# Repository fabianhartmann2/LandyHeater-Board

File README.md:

# LandyHeater Board

Hardwareentwicklung für das Landy-Heater-Steuergerät auf Basis des `ESP32-S3-WROOM-1U-N16R8`.

## Aktueller Stand

Revision A hat Phase 0 und Phase 1 abgeschlossen. Der Phase-2-Schaltplan wurde nach dem zurückgewiesenen rasterartigen Erstentwurf grundlegend als zusammenhängender Engineering-Schaltplan neu aufgebaut. Alle sieben A4-Seiten wurden aus dem KiCad-Export einzeln visuell geprüft; lokale Funktionsnetze werden mit sichtbaren Leitungen dargestellt. ERC, Struktur-Audit und der elektrische Vorher-/Nachher-Netzlistenvergleich sind fehlerfrei. Die normative Grundlage ist Dokumentversion 1.6. Phase 2 bleibt wegen der im Review dokumentierten Mess-, Transienten-, FPC- und Footprint-Gates sowie der noch ausstehenden ausdrücklichen Abnahme **nicht freigegeben**; Phase 3 wurde nicht begonnen.

- [Hardware-Anforderungsspezifikation Revision A](docs/Hardware-Anforderungsspezifikation_Revision_A.md)
- [Ergebnisbericht Phase 0](docs/Phase_0_KiCad-Arbeitsumgebung.md)
- [Phase 1 – Architektur und Bauteilfestlegung](docs/Phase_1_Architektur-und-Bauteilfestlegung.md)
- [Phase 2 – KiCad-Schaltplan und Review](docs/Phase_2_Schaltplanreview.md)
- [Phase 2 – Anforderungs- und Schnittstellenliste](docs/Phase_2_Anforderungs-und-Schnittstellenliste.md)
- [Phase 2 – Quellen und Rückverfolgbarkeit](docs/Phase_2_Quellen-und-Rueckverfolgbarkeit.md)
- [GPIO-Matrix Revision A](docs/GPIO-Matrix_Revision_A.md)
- [Leistungs- und Ruhestrombudget Revision A](calculations/Leistungs-und-Ruhestrombudget_Revision_A.md)
- [Phase 2 – Worst-Case-Berechnungen](calculations/Phase_2_Worst-Case-Berechnungen.md)
- [Schaltplan-PDF Phase 2](output/pdf/LandyHeater-Board-schematic-Phase2.pdf)
- [Vorläufige BOM Phase 2](output/bom/LandyHeater-Board-BOM-Phase2.csv)
- [ERC-Bericht Phase 2](output/reports/LandyHeater-Board-ERC-Phase2.rpt)
- [Netzlisten-/BOM-Audit Phase 2](output/reports/LandyHeater-Board-Audit-Phase2.txt)
- [Netzlistenvergleich vor/nach grafischer Überarbeitung](output/reports/LandyHeater-Board-Netlist-Comparison-Phase2.txt)

Die Spezifikation definiert Funktionsumfang, Schnittstellen, Versorgung, Mechanik, sichere Hardwarezustände, Layoutregeln, Fertigungsunterlagen und Abnahmetests. Die darin aufgeführten Verifikationspunkte müssen vor der Fertigungsfreigabe abgeschlossen werden.

## Phasenplan Revision A

Jede Phase wird einzeln beauftragt, geprüft und freigegeben. Mit der nächsten Phase wird erst nach ausdrücklicher Freigabe der Ergebnisse begonnen. Erkenntnisse, die Anforderungen verändern, werden zuerst in der Hardware-Anforderungsspezifikation dokumentiert.

### Phase 0 – KiCad-Arbeitsumgebung und Projektgerüst

- KiCad-10-Version und Kommandozeilenwerkzeuge prüfen und dokumentieren.
- Verzeichnisstruktur für KiCad-Quellen, lokale Symbole, Footprints, 3D-Modelle, Berechnungen und Fertigungsdaten anlegen.
- Leeres KiCad-Projekt mit vier Lagen, Revision, Titelblock und grundlegenden Netzklassen erstellen.
- Reproduzierbare Prüf- und Exportbefehle vorbereiten.

**Freigabepunkt:** Das Projekt lässt sich ohne fehlende Bibliotheken öffnen und die automatischen KiCad-Prüfwerkzeuge sind verfügbar.

**Status:** Technisch abgeschlossen und durch den Auftraggeber am 06.09.2026 mit dem Auftrag zum Beginn von Phase 1 freigegeben.

### Phase 1 – Schaltungsarchitektur und Bauteilfestlegung

- Blockschaltbild, Versorgungskonzept und Spannungsdomänen finalisieren.
- Vollständige ESP32-GPIO-Matrix einschließlich Reset-, Boot- und Deep-Sleep-Zuständen erstellen.
- Strom-, Ruhestrom-, Verlustleistungs- und USB-Lastbudget erstellen.
- Konkrete Herstellerteilenummern für aktive Bauteile, Schutzbeschaltung, Steckverbinder und FPC-Stecker auswählen.
- Footprints, Pinouts, Temperaturbereiche und PCBWay-Beschaffbarkeit vorprüfen.

**Freigabepunkt:** Architektur, GPIO-Matrix, Bauteilauswahl und Berechnungen sind nachvollziehbar dokumentiert; offene Punkte für den Schaltplan sind geschlossen oder ausdrücklich als Verifikationspunkte gekennzeichnet.

**Status:** Technisch abgeschlossen und durch den Auftraggeber am 06.09.2026 mit dem Auftrag zum Beginn von Phase 2 freigegeben.

### Phase 2 – KiCad-Schaltplan

- Hierarchischen Schaltplan für Versorgung, ESP32/USB, Display/Touch/Frontlicht, RTC, AUTOTERM, 1-Wire, Taster/LED und Diagnoseanzeige erstellen.
- Lokale Symbole und Footprint-Zuordnungen vollständig einbinden.
- Sichere Hardwarezustände, Testpunkte und Bestückungsoptionen abbilden.
- ERC durchführen und alle Warnungen entweder beheben oder schriftlich begründen.
- Schaltplan-PDF und vorläufige BOM für den Review erzeugen.

**Freigabepunkt:** Schaltplanreview abgeschlossen, ERC ohne ungeklärte Fehler und alle Hersteller-Pinouts unabhängig geprüft.

**Status:** Grafischer Neuaufbau, interner A4-Sichtreview und elektrischer Review abgeschlossen. ERC, exportierter Netzlisten-/BOM-Audit und Vorher-/Nachher-Topologievergleich sind fehlerfrei. Phase 2 ist dennoch nicht freigegeben, bis die in `docs/Phase_2_Schaltplanreview.md` aufgeführten Freigabesperren geschlossen und der Schaltplan ausdrücklich abgenommen ist.

### Phase 3 – Mechanik und Platzierung

- PCB-Kontur, Befestigungspunkte und zulässigen Bauraum festlegen.
- Display, drei FPC-Stecker, Nano-Fit-Anschlüsse, USB-C, Antennenkoax, Knopfzelle sowie BOOT-, RESET- und DIAG-Taster platzieren.
- Energiefluss-Diagnoseanzeige und gegebenenfalls zwei optionale Status-LEDs integrieren.
- Kritische Keep-outs, FPC-Biegeradien, Steck-/Entriegelungswege und Servicezugang prüfen.
- Vollständig bestücktes 3D-STEP-Modell für Gehäuse- und Kollisionsprüfung erzeugen.

**Freigabepunkt:** Platzierungs- und 3D-Review abgeschlossen; Gehäuseschnittstellen, Bedienung und Wartungszugang sind freigegeben.

### Phase 4 – Vierlagen-PCB-Layout

- Finalen PCBWay-Stackup und Netzklassen übernehmen.
- Versorgungsschutz, Buck-Regler, USB, ESP32, E-Paper-Booster und weitere Signale nach Priorität routen.
- Durchgehende GND-Referenz, Rückstrompfade, Abblockung, EMI-Abstände und thermische Reserven sicherstellen.
- DRC, ERC-Rückprüfung, Layoutchecklisten und visuellen Lagenreview durchführen.

**Freigabepunkt:** DRC ohne ungeklärte Fehler; Schaltplan, PCB, Pin-Matrix und BOM sind synchron und der Layoutreview ist dokumentiert.

### Phase 5 – PCBWay-Fertigungsfreigabe

- RS-274-X-Gerber, Excellon-Bohrdaten und gegebenenfalls ODB++/IPC-D-356 erzeugen.
- PCBWay-BOM und CPL/Centroid-Dateien mit Seite, Position und Rotation erstellen.
- Schaltplan, Bestückungszeichnungen, Fertigungszeichnung, DNP-Liste, STEP-Modell und spezielle Prozesshinweise beilegen.
- Gerber, Bohrungen, Lötstoppmaske, Pastenlagen, Silkscreen, Bauteilrotationen und Pin 1 unabhängig kontrollieren.
- Getrennte, eindeutig versionierte ZIP-Pakete für PCB-Fertigung und PCBA zusammenstellen.

**Freigabepunkt:** Manufacturing-Release-Checkliste vollständig; erst danach dürfen die fünf Prototypen bei PCBWay bestellt werden.

### Phase 6 – Inbetriebnahme der fünf Prototypen

- Sicht-, Kurzschluss- und Widerstandsprüfung vor dem ersten Einschalten.
- Versorgungsschienen mit strombegrenzten Laborquellen stufenweise prüfen.
- ESP32-Reset, Boot und USB-Programmierung verifizieren.
- Diagnoseanzeige, Deep-Sleep, RTC, Touch, Display, Frontlicht, 1-Wire und AUTOTERM in definierter Reihenfolge testen.
- Ruhestrom, Lastsprünge, Rückspeisung, Temperaturverhalten und alle Abnahmekriterien protokollieren.
- Abweichungen sammeln und Entscheidung über Nacharbeit oder Revision B treffen.

**Freigabepunkt:** Vollständiger Prüfbericht für alle fünf Prototypen und dokumentierte Entscheidung über den weiteren Einsatz.

### Geplante Endergebnisse

- editierbares KiCad-Projekt mit projektlokalen Bibliotheken,
- Schaltplan und Bestückungszeichnungen als PDF,
- vollständige BOM und GPIO-Matrix,
- PCB-Layout und 3D-STEP-Modell,
- Gerber-, Drill-, CPL-/Centroid- und PCBWay-BOM-Dateien,
- Fertigungs- und PCBA-ZIP-Pakete,
- Prüfplan und Prototypen-Prüfbericht.

## Abgrenzung Revision A

Revision A umfasst die AUTOTERM-UART-Schnittstelle, drei gemeinsam angeschlossene DS18B20-Sensoren, RTC, USB-C, externen Taster mit dimmbarer LED, eine lokale Energiefluss-Diagnoseanzeige sowie das Good-Display-E-Paper mit Touch und Frontlicht. VOTRONIC VBCS und Smart-Shunt sind für eine spätere Revision vorgemerkt.

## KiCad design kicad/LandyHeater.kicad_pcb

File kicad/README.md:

# LandyHeater Controller – KiCad-Projekt (Rev B)

Neuaufbau nach [Anforderungsdokument v2.0](../docs/Anforderungsdokument_Neuentwicklung.md). Aus dem bisherigen Repository wurden keine KiCad-Dateien, Bibliotheken oder Skripte übernommen (N-01).

## Stand

| Phase | Status |
|---|---|
| 0 – Projekt, Lagen, Regeln, Bibliotheken | freigegeben (2026-10-12) |
| 1 – Bauteilauswahl, Symbole, Footprints | freigegeben (2026-10-12) – [Bauteilliste](Bauteilliste.md) |
| 2 – Schaltplan | freigegeben (2026-10-13) – [Review](Phase2_Schaltplanreview.md), [Entwurf](Schaltungsentwurf.md) |
| 3 – Platzierung (Meilenstein nach [Layout-Anleitung](../docs/PCB_Layout_Engineering_Instructions.md)) | Schritt 1–2 freigegeben: [Analyse und Floorplan](Platzierung_1_Analyse_Floorplan.md) · Schritt 3–5 freigegeben (2026-10-14): [Platzierungsbericht](Platzierung_2_Bericht.md) · Schritt 6 Routing in Arbeit · [Transientennachweis V-01](Phase3_Platzierung.md#6-transientennachweis-v-01-p-03) |

## Struktur

| Pfad | Inhalt |
|---|---|
| `LandyHeater.kicad_pro/.kicad_sch/.kicad_pcb` | Projekt, Schaltplan, Leiterplatte (KiCad 10.0) |
| `libraries/LandyHeater.kicad_sym` | projektlokale, geprüfte Symbole (Bibliothek `LandyHeater`) |
| `libraries/LandyHeater.pretty/` | projektlokale, geprüfte Footprints (Bibliothek `LandyHeater`) |
| `libraries/3dmodels/` | 3D-Modelle, im Projekt als `${LANDYHEATER_3DMODELS}` |
| `tools/` | reproduzierbare KiCad-Python-Werkzeuge: Floorplan, Platzierung, Platzierungsprüfung, Ratsnest-Kennzahlen, Footprint-Aktualisierung |
| `sim/` | SPICE-Nachweise (ngspice aus KiCad) |
| `doc/` | Renderings für die Berichte |
| `output/` | erzeugte Berichte und Fertigungsdaten (nicht versioniert) |

## Leiterplatte

- 4 Lagen, JLCPCB-Stackup **JLC04161H-7628**, 1,6 mm, ENIG:
  F.Cu 35 µm · Prepreg 7628 0,2104 mm (εr 4,4) · In1.Cu 15,2 µm · Kern 1,065 mm · In2.Cu 15,2 µm · Prepreg 0,2104 mm · B.Cu 35 µm.
- Lagennutzung (A14): F.Cu Bauteile/Signale, In1.Cu GND durchgehend, In2.Cu Versorgung/langsame Signale, B.Cu GND/langsame Signale.
- Kontur: 80 × 50 mm, Ecken R 2 mm, Ursprung (100, 100). Vier M3-Befestigungslöcher H1–H4 (3,2 mm, nur Leiterplatte) in den Ecken, drei Passermarken FID1–FID3.

## Designregeln (JLCPCB 4 Lagen, mit Reserve)

| Regel | Wert | JLCPCB-Minimum |
|---|---|---|
| Leiterbahn Standard / Minimum | 0,2 / 0,127 mm | 0,09 mm |
| Abstand Kupfer | 0,2 mm (Regel), in Feinraster-ICs 0,12 mm | 0,09 mm |
| Via Standard | 0,6 / 0,3 mm | 0,45 / 0,3 mm (ohne Aufpreis) |
| Via Minimum | 0,45 / 0,3 mm | – |
| Kupfer zum Platinenrand | 0,3 mm | 0,2 mm |
| Bohrung zu Kupfer | 0,25 mm (Regel), USB-C-Führungsstifte 0,15 mm | – |
| Bohrung Minimum | 0,2 mm (Wärmevias ESP32-Modul) | 0,15 mm |
| Courtyard | Pflicht (Fehler) | – |

## Netzklassen

| Klasse | Bahn | Abstand | Via | Zuordnung (Muster) |
|---|---|---|---|---|
| Default | 0,2 mm | 0,2 mm | 0,6/0,3 | alle übrigen Netze |
| Power | 0,65 mm (G-01) | 0,2 mm | 0,8/0,4 | `BATT_12V_IN`, `12V_PROT`, `VIN_SYS`, `USB_VBUS`, `VBUS_PROT`, `3V3_CORE`, `SW_BUCK` |
| USB | Diff.-Paar 0,25 mm / Spalt 0,13 mm | 0,2 mm (im Paar 0,13 mm) | 0,6/0,3 | `USB_D*` |
| Extern | 0,3 mm | 0,2 mm | 0,6/0,3 | `AUTOTERM_*`, `CTRL_*`, `1WIRE_DQ`, `3V3_SENSOR_SW`, `BUTTON_N`, `LED_CC_PLUS`, `LED_PWM_MINUS` |

Die Abstände kommen aus `LandyHeater.kicad_dru`: KiCad verwendet den größeren Wert aus Netzklasse und Regel, deshalb stehen die Netzklassen auf 0,15 mm und die Regel setzt 0,2 mm mit den begründeten Ausnahmen.

Das USB-Paar ist für ≈ 90 Ω differentiell über In1.Cu (Abstand 0,2104 mm) abgeschätzt. Vor dem Routing mit dem JLCPCB-Impedanzrechner für JLC04161H-7628 bestätigen und die Werte gegebenenfalls anpassen. Netznamen in den Mustern sind die geplanten Namen aus dem Anforderungsdokument; neue Netze werden bei Bedarf ergänzt.

## Prüfregeln

Alle ERC-Prüfungen sind aktiv, einschließlich der SPICE-Modellprüfung (Warnung): Jedes Symbol braucht ein SPICE-Modell oder eine begründete Abschaltung (`Sim.Enable` = 0, z. B. Steckverbinder, Testpunkte, Module ohne Herstellermodell). Im DRC sind nur die KiCad-Standardausnahmen „track not centered on via“ und „tuning profile track geometries“ ausgeblendet.

## Prüf- und Exportbefehle

```bash
KICAD_CLI=/Applications/KiCad/KiCad.app/Contents/MacOS/kicad-cli
$KICAD_CLI sch erc -o output/erc.rpt LandyHeater.kicad_sch
$KICAD_CLI pcb drc --schematic-parity -o output/drc.rpt LandyHeater.kicad_pcb
$KICAD_CLI sch export netlist -o output/LandyHeater.net LandyHeater.kicad_sch
$KICAD_CLI sch export pdf -o output/LandyHeater-schematic.pdf LandyHeater.kicad_sch
$KICAD_CLI sch export bom -o output/LandyHeater-bom.csv LandyHeater.kicad_sch
$KICAD_CLI pcb export gerbers -o output/gerber/ LandyHeater.kicad_pcb
$KICAD_CLI pcb export drill -o output/gerber/ LandyHeater.kicad_pcb
$KICAD_CLI pcb export pos --side front --format csv --units mm -o output/LandyHeater-cpl.csv LandyHeater.kicad_pcb
$KICAD_CLI pcb export step -o output/LandyHeater.step LandyHeater.kicad_pcb
```

Die Netzlistenprüfung nach N-05 erfolgt anhand der exportierten Netzliste gegen das Anforderungsdokument. Für JLCPCB werden BOM (mit Spalte `LCSC`) und CPL in Phase 5 in das JLCPCB-Format gebracht.

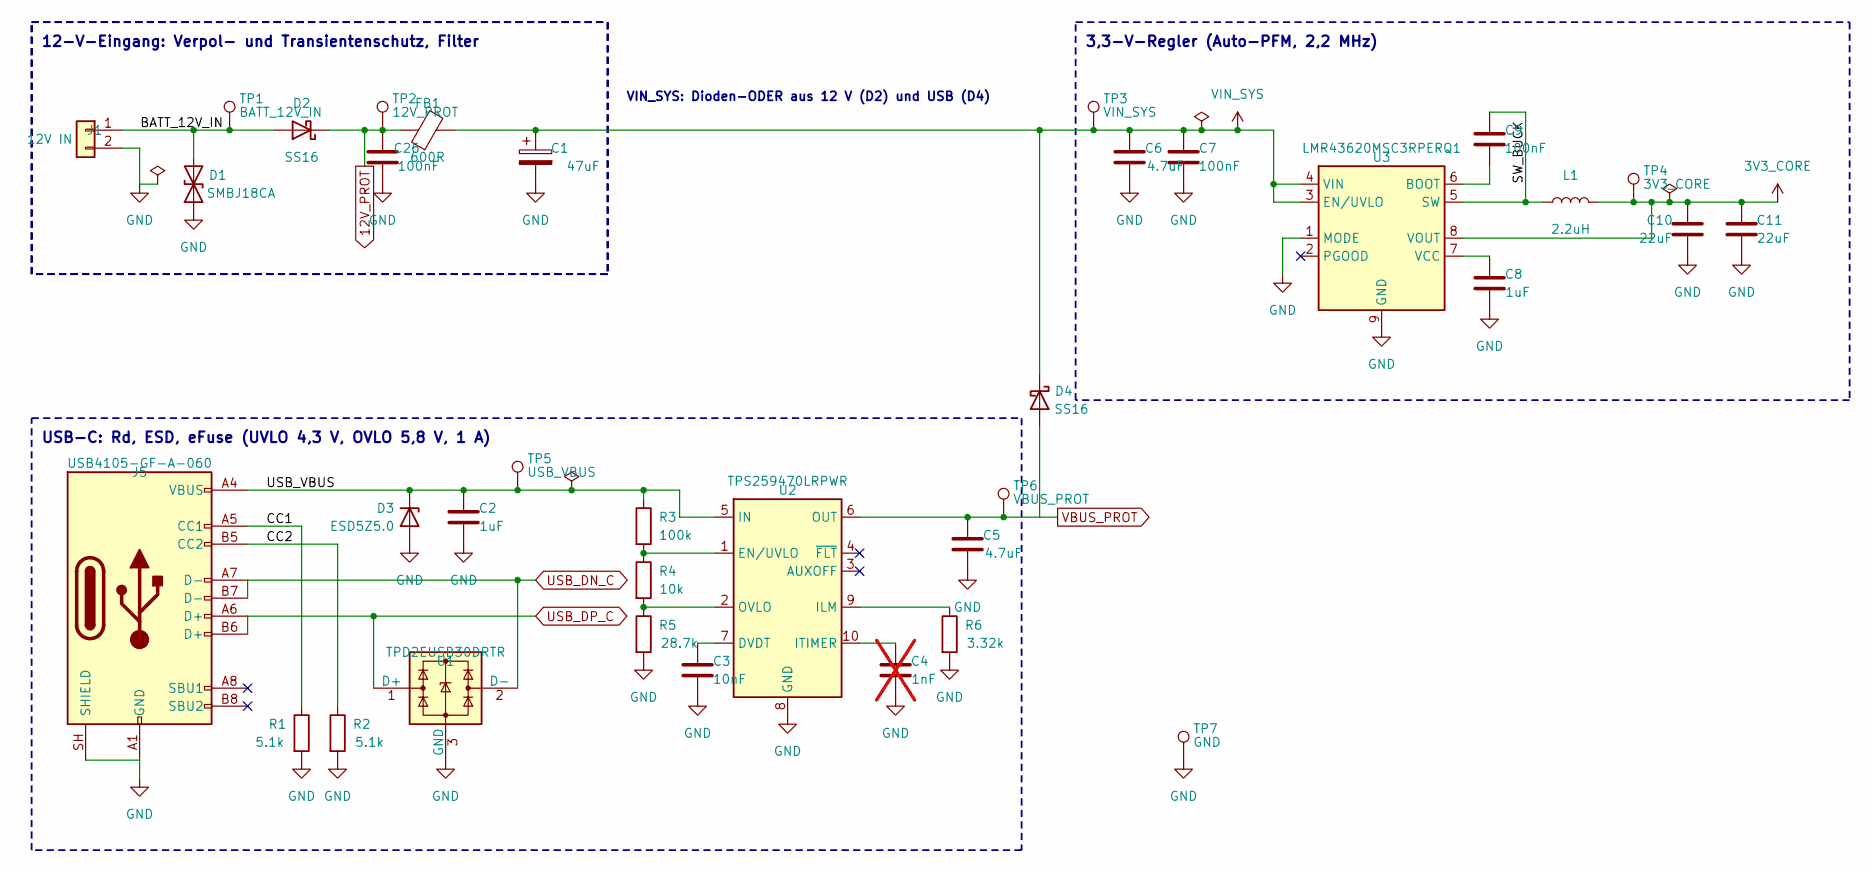
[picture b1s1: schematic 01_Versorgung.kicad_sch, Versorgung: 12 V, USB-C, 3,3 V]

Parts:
C1: 47uF; CP_Elec_6.3x7.7
C2, C8: 1uF; C_0603_1608Metric
C3: 10nF; C_0603_1608Metric
C4: 1nF; C_0603_1608Metric; not fitted
C5: 4.7uF; C_0603_1608Metric
C6: 4.7uF; C_1206_3216Metric
C7, C9, C26: 100nF; C_0603_1608Metric
C10, C11: 22uF; C_1206_3216Metric
D1: SMBJ18CA; D_SMB; MPN SMBJ18CA; LCSC C78413
D2, D4: SS16; D_SMA; MPN SS16; LCSC C2481
D3: ESD5Z5.0; D_SOD-523; MPN ESD5Z5.0T1G; LCSC C82044
FB1: 600R; L_0805_2012Metric
J1: 12V IN; Molex_Nano-Fit_105313-xx02_1x02_P2.50mm_Horizontal; MPN 1053131302; LCSC C17345480
J5: USB4105-GF-A-060; USB_C_Receptacle_GCT_USB4105-xx-A_16P_TopMnt_Horizontal; MPN USB4105-GF-A-060; LCSC C3025063
L1: 2.2uH; L_CJiang_FAUL0420; MPN FAUL0420-2R2MT; LCSC C3040383
R1, R2: 5.1k; R_0603_1608Metric
R3: 100k; R_0603_1608Metric
R4: 10k; R_0603_1608Metric
R5: 28.7k; R_0603_1608Metric
R6: 3.32k; R_0603_1608Metric
TP1: BATT_12V_IN; TestPoint_Pad_D1.5mm
TP2: 12V_PROT; TestPoint_Pad_D1.5mm
TP3: VIN_SYS; TestPoint_Pad_D1.5mm
TP4: 3V3_CORE; TestPoint_Pad_D1.5mm
TP5: USB_VBUS; TestPoint_Pad_D1.5mm
TP6: VBUS_PROT; TestPoint_Pad_D1.5mm
TP7: GND; TestPoint_Pad_D1.5mm
U1: TPD2EUSB30DRTR; Texas_DRT-3; MPN TPD2EUSB30DRTR; LCSC C97502
U2: TPS259470LRPWR; TI_RPW0010A_VQFN-HR-10_2x2mm; MPN TPS259470LRPWR; LCSC C3662793
U3: LMR43620MSC3RPERQ1; TI_RPE0009A_VQFN-HR-9_2x2mm; MPN LMR43620MSC3RPERQ1; LCSC C3190193

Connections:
3V3_CORE: C10.1, C11.1, L1.2, TP4.1 (1_1), U3.8 (VOUT); also elsewhere on the board
12V_PROT: C26.1, D2.1 (K), FB1.1, TP2.1 (1_1); also elsewhere on the board
/Versorgung/BATT_12V_IN: D1.2 (A2), D2.2 (A), J1.1, TP1.1 (1_1)
/Versorgung/CC1: J5.A5 (CC1), R1.1
/Versorgung/CC2: J5.B5 (CC2), R2.1
/Versorgung/SW_BUCK: C9.1, L1.1, U3.5 (SW)
/Versorgung/USB_VBUS: C2.1, D3.1 (K), J5.A4 (VBUS), J5.A9 (VBUS), J5.B4 (VBUS), J5.B9 (VBUS), R3.1, TP5.1 (1_1), U2.5 (IN)
GND: C1.2, C2.2, C3.2, C4.2, C5.2, C6.2, C7.2, C8.2, C10.2, C11.2, C26.2, D1.1 (A1), D3.2 (A), J1.2, J5.A1 (GND), J5.A12 (GND), J5.B1 (GND), J5.B12 (GND), J5.SH (SHIELD), R1.2, R2.2, R5.2, R6.2, TP7.1 (1_1), U1.3 (GND), U2.8 (GND), U3.1 (MODE), U3.9 (GND); also elsewhere on the board
unnamed: C3.1, U2.7 (DVDT)
unnamed: R3.2, R4.1, U2.1 (EN/UVLO)
unnamed: R6.1, U2.9 (ILM)
unnamed: C4.1, U2.10 (ITIMER)
unnamed: R4.2, R5.1, U2.2 (OVLO)
unnamed: C9.2, U3.6 (BOOT)
unnamed: C8.1, U3.7 (VCC)
USB_DN_C: J5.A7 (D-), J5.B7 (D-), U1.2 (D-); also elsewhere on the board
USB_DP_C: J5.A6 (D+), J5.B6 (D+), U1.1 (D+); also elsewhere on the board
VBUS_PROT: C5.1, D4.2 (A), TP6.1 (1_1), U2.6 (OUT); also elsewhere on the board
VIN_SYS: C1.1, C6.1, C7.1, D4.1 (K), FB1.2, TP3.1 (1_1), U3.3 (EN/UVLO), U3.4 (VIN); also elsewhere on the board

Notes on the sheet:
VIN_SYS: Dioden-ODER aus 12 V (D2) und USB (D4)
12-V-Eingang: Verpol- und Transientenschutz, Filter
USB-C: Rd, ESD, eFuse (UVLO 4,3 V, OVLO 5,8 V, 1 A)
3,3-V-Regler (Auto-PFM, 2,2 MHz)

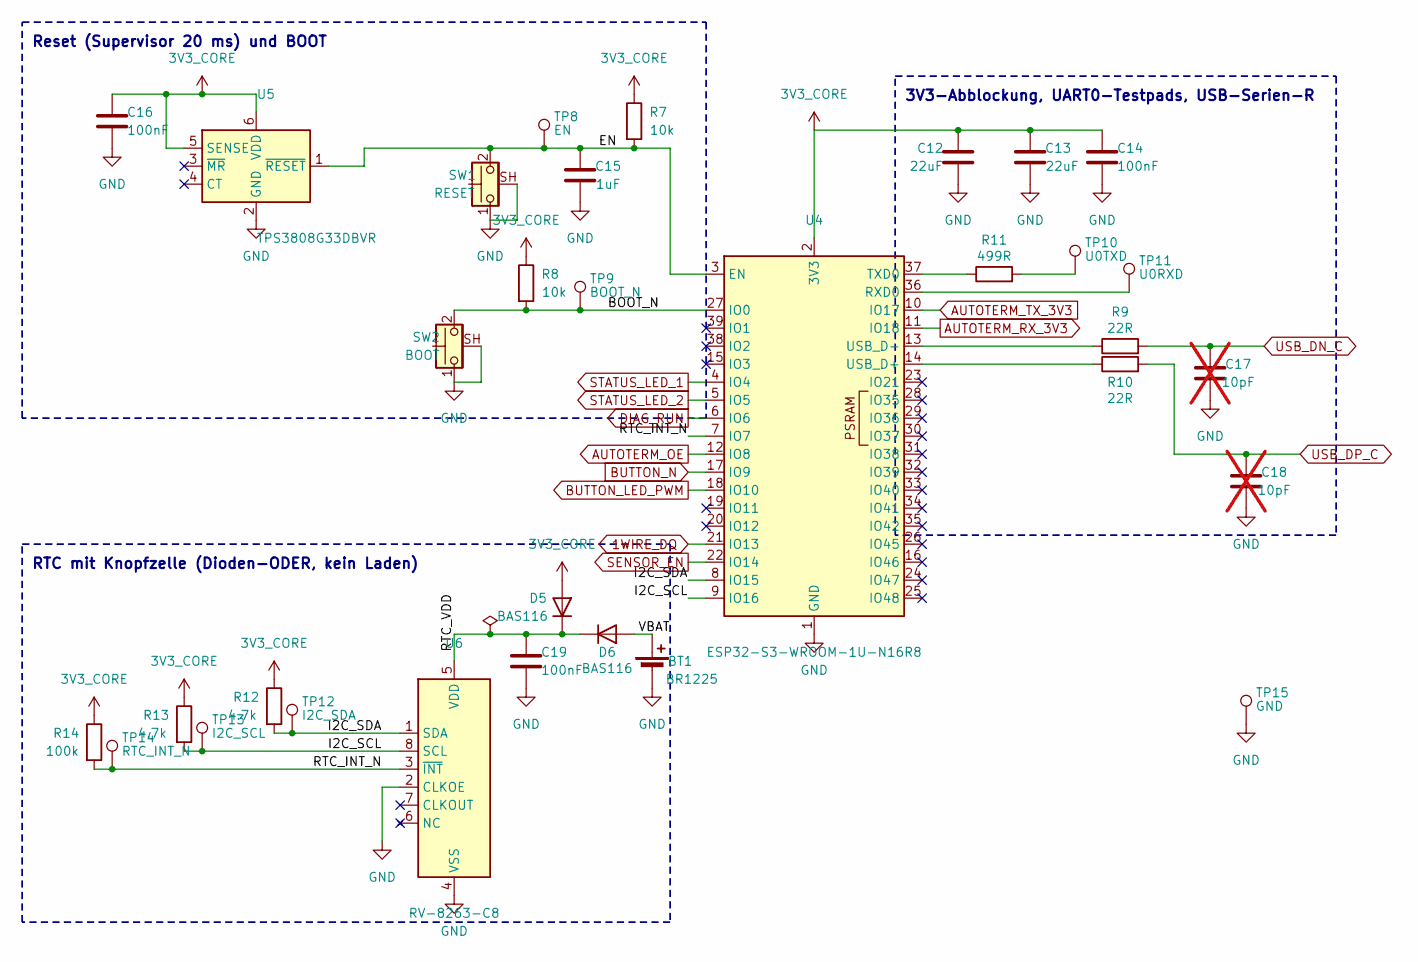
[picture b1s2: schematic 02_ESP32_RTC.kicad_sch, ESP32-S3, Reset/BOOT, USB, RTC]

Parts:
BT1: BR1225; BatteryClip_MYOUNG_MY-1225-01-J; MPN MY-1225-01-J; LCSC C20606803
C12, C13: 22uF; C_1206_3216Metric
C14, C16, C19: 100nF; C_0603_1608Metric
C15: 1uF; C_0603_1608Metric
C17, C18: 10pF; C_0603_1608Metric; not fitted
D5, D6: BAS116; SOT-23; MPN BAS116,215; LCSC C48502
R7, R8: 10k; R_0603_1608Metric
R9, R10: 22R; R_0603_1608Metric
R11: 499R; R_0603_1608Metric
R12, R13: 4.7k; R_0603_1608Metric
R14: 100k; R_0603_1608Metric
SW1: RESET; SW_Push_1P1T-SH_NO_CK_KMR2xxG; MPN KMR221GLFS; LCSC C72443
SW2: BOOT; SW_Push_1P1T-SH_NO_CK_KMR2xxG; MPN KMR221GLFS; LCSC C72443
TP8: EN; TestPoint_Pad_D1.5mm
TP9: BOOT_N; TestPoint_Pad_D1.5mm
TP10: U0TXD; TestPoint_Pad_D1.5mm
TP11: U0RXD; TestPoint_Pad_D1.5mm
TP12: I2C_SDA; TestPoint_Pad_D1.5mm
TP13: I2C_SCL; TestPoint_Pad_D1.5mm
TP14: RTC_INT_N; TestPoint_Pad_D1.5mm
TP15: GND; TestPoint_Pad_D1.5mm
U4: ESP32-S3-WROOM-1U-N16R8; ESP32-S3-WROOM-1U; MPN ESP32-S3-WROOM-1U-N16R8; LCSC C3013946
U5: TPS3808G33DBVR; SOT-23-6; MPN TPS3808G33DBVR; LCSC C51886189
U6: RV-8263-C8; MicroCrystal_C8_SON-8_2.0x1.2mm; MPN RV-8263-C8-32.768KHZ-20PPM-TA-QC; LCSC C24955831

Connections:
1WIRE_DQ: U4.21 (IO13); also elsewhere on the board
3V3_CORE: C12.1, C13.1, C14.1, C16.1, D5.1 (A), R7.1, R8.1, R12.1, R13.1, R14.1, U4.2 (3V3), U5.5 (SENSE), U5.6 (VDD); also elsewhere on the board
/ESP32 und RTC/BOOT_N: R8.2, SW2.2, TP9.1 (1_1), U4.27 (IO0)
/ESP32 und RTC/EN: C15.1, R7.2, SW1.2, TP8.1 (1_1), U4.3 (EN), U5.1 (~RESET)
/ESP32 und RTC/I2C_SCL: R13.2, TP13.1 (1_1), U4.9 (IO16), U6.8 (SCL)
/ESP32 und RTC/I2C_SDA: R12.2, TP12.1 (1_1), U4.8 (IO15), U6.1 (SDA)
/ESP32 und RTC/RTC_INT_N: R14.2, TP14.1 (1_1), U4.7 (IO7), U6.3 (~INT)
/ESP32 und RTC/RTC_VDD: C19.1, D5.3 (K), D6.3 (K), U6.5 (VDD)
/ESP32 und RTC/VBAT: BT1.1 (+), D6.1 (A)
AUTOTERM_OE: U4.12 (IO8); also elsewhere on the board
AUTOTERM_RX_3V3: U4.11 (IO18); also elsewhere on the board
AUTOTERM_TX_3V3: U4.10 (IO17); also elsewhere on the board
BUTTON_LED_PWM: U4.18 (IO10); also elsewhere on the board
BUTTON_N: U4.17 (IO9); also elsewhere on the board
DIAG_RUN: U4.6 (IO6); also elsewhere on the board
GND: BT1.2 (-), C12.2, C13.2, C14.2, C15.2, C16.2, C17.2, C18.2, C19.2, SW1.1, SW1.SH (B), SW2.1, SW2.SH (B), TP15.1 (1_1), U4.1 (GND), U4.40 (GND), U4.41 (GND), U5.2 (GND), U6.2 (CLKOE), U6.4 (VSS); also elsewhere on the board
unnamed: R11.2, TP10.1 (1_1)
unnamed: TP11.1 (1_1), U4.36 (RXD0)
unnamed: R11.1, U4.37 (TXD0)
unnamed: R10.1, U4.14 (USB_D+)
unnamed: R9.1, U4.13 (USB_D-)
SENSOR_EN: U4.22 (IO14); also elsewhere on the board
STATUS_LED_1: U4.4 (IO4); also elsewhere on the board
STATUS_LED_2: U4.5 (IO5); also elsewhere on the board
USB_DN_C: C17.1, R9.2; also elsewhere on the board
USB_DP_C: C18.1, R10.2; also elsewhere on the board

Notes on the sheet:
3V3-Abblockung, UART0-Testpads, USB-Serien-R
Reset (Supervisor 20 ms) und BOOT
RTC mit Knopfzelle (Dioden-ODER, kein Laden)

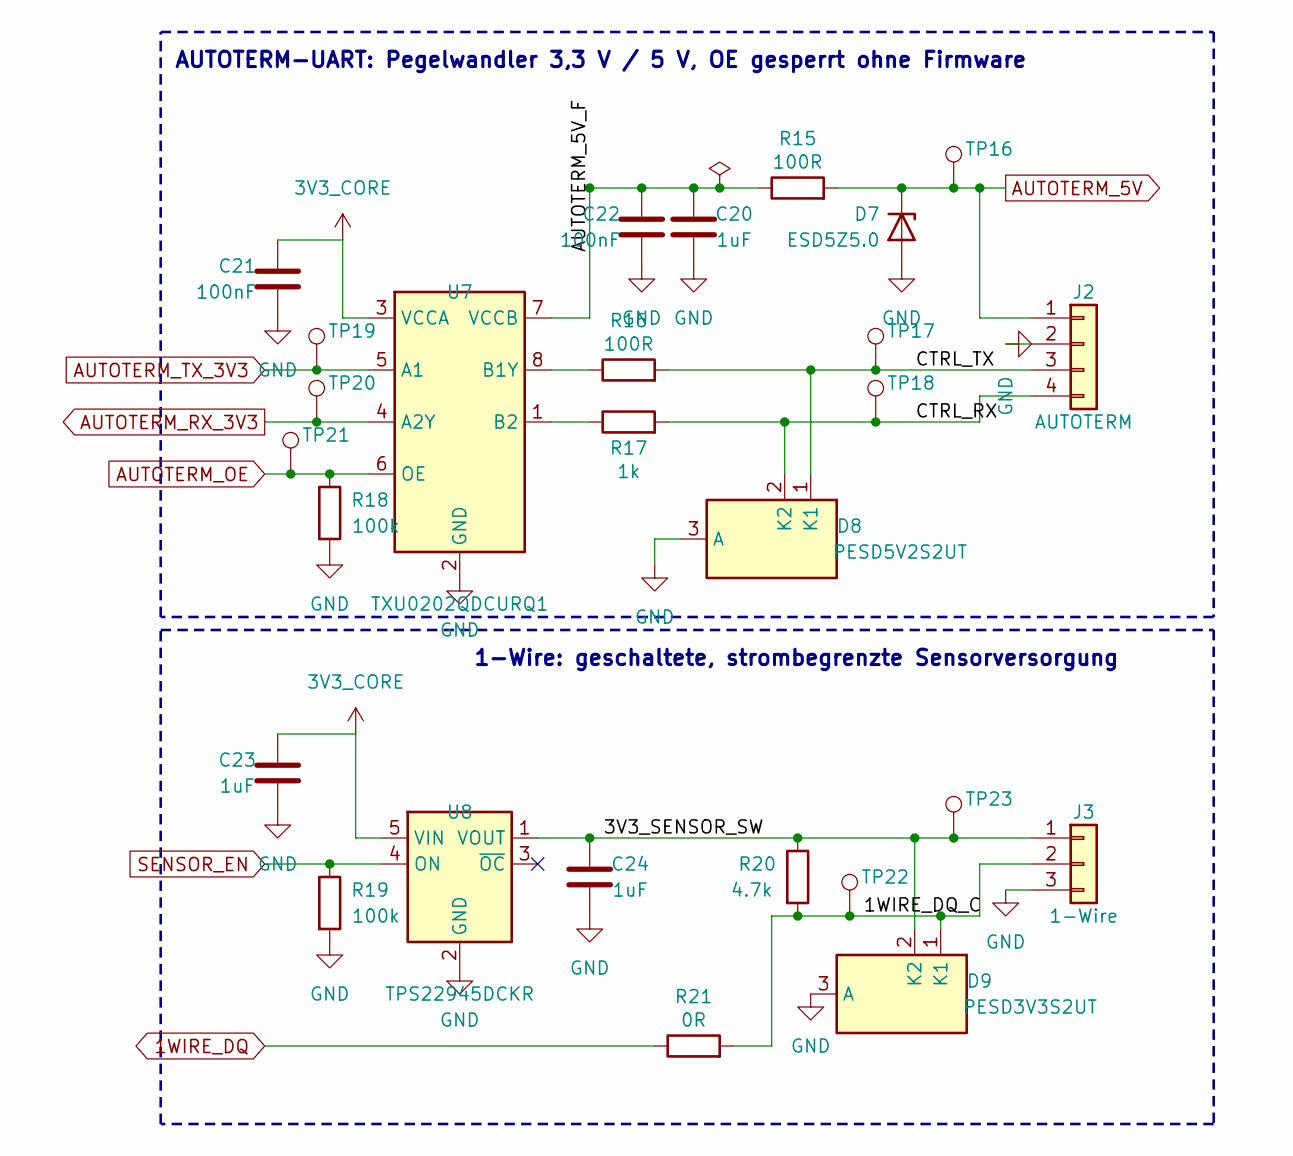
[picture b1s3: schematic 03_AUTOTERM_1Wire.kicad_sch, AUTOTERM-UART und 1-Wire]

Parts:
C20, C23, C24: 1uF; C_0603_1608Metric
C21, C22: 100nF; C_0603_1608Metric
D7: ESD5Z5.0; D_SOD-523; MPN ESD5Z5.0T1G; LCSC C82044
D8: PESD5V2S2UT; SOT-23; MPN PESD5V2S2UT,215; LCSC C18441
D9: PESD3V3S2UT; SOT-23; MPN PESD3V3S2UT,215; LCSC C84276
J2: AUTOTERM; Molex_Nano-Fit_105313-xx04_1x04_P2.50mm_Horizontal; MPN 1053131304; LCSC C17554326
J3: 1-Wire; Molex_Nano-Fit_105313-xx03_1x03_P2.50mm_Horizontal; MPN 1053131303; LCSC C17198650
R15, R16: 100R; R_0603_1608Metric
R17: 1k; R_0603_1608Metric
R18, R19: 100k; R_0603_1608Metric
R20: 4.7k; R_0603_1608Metric
R21: 0R; R_0603_1608Metric
TP16: AUTOTERM_5V; TestPoint_Pad_D1.5mm
TP17: CTRL_TX; TestPoint_Pad_D1.5mm
TP18: CTRL_RX; TestPoint_Pad_D1.5mm
TP19: TX_3V3; TestPoint_Pad_D1.5mm
TP20: RX_3V3; TestPoint_Pad_D1.5mm
TP21: OE; TestPoint_Pad_D1.5mm
TP22: 1WIRE_DQ_C; TestPoint_Pad_D1.5mm
TP23: 3V3_SENSOR_SW; TestPoint_Pad_D1.5mm
U7: TXU0202QDCURQ1; VSSOP-8_2.3x2mm_P0.5mm; MPN TXU0202QDCURQ1; LCSC C7372013
U8: TPS22945DCKR; SOT-353_SC-70-5; MPN TPS22945DCKR; LCSC C47507

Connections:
1WIRE_DQ: R21.1; also elsewhere on the board
3V3_CORE: C21.1, C23.1, U7.3 (VCCA), U8.5 (VIN); also elsewhere on the board
/AUTOTERM und 1-Wire/1WIRE_DQ_C: D9.1 (K1), J3.2, R20.2, R21.2, TP22.1 (1_1)
/AUTOTERM und 1-Wire/3V3_SENSOR_SW: C24.1, D9.2 (K2), J3.1, R20.1, TP23.1 (1_1), U8.1 (VOUT)
/AUTOTERM und 1-Wire/AUTOTERM_5V_F: C20.1, C22.1, R15.1, U7.7 (VCCB)
/AUTOTERM und 1-Wire/CTRL_RX: D8.2 (K2), J2.4, R17.2, TP18.1 (1_1)
/AUTOTERM und 1-Wire/CTRL_TX: D8.1 (K1), J2.3, R16.2, TP17.1 (1_1)
AUTOTERM_5V: D7.1 (K), J2.1, R15.2, TP16.1 (1_1); also elsewhere on the board
AUTOTERM_OE: R18.1, TP21.1 (1_1), U7.6 (OE); also elsewhere on the board
AUTOTERM_RX_3V3: TP20.1 (1_1), U7.4 (A2Y); also elsewhere on the board
AUTOTERM_TX_3V3: TP19.1 (1_1), U7.5 (A1); also elsewhere on the board
GND: C20.2, C21.2, C22.2, C23.2, C24.2, D7.2 (A), D8.3 (A), D9.3 (A), J2.2, J3.3, R18.2, R19.2, U7.2 (GND), U8.2 (GND); also elsewhere on the board
unnamed: R16.1, U7.8 (B1Y)
unnamed: R17.1, U7.1 (B2)
SENSOR_EN: R19.1, U8.4 (ON); also elsewhere on the board

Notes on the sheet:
AUTOTERM-UART: Pegelwandler 3,3 V / 5 V, OE gesperrt ohne Firmware
1-Wire: geschaltete, strombegrenzte Sensorversorgung

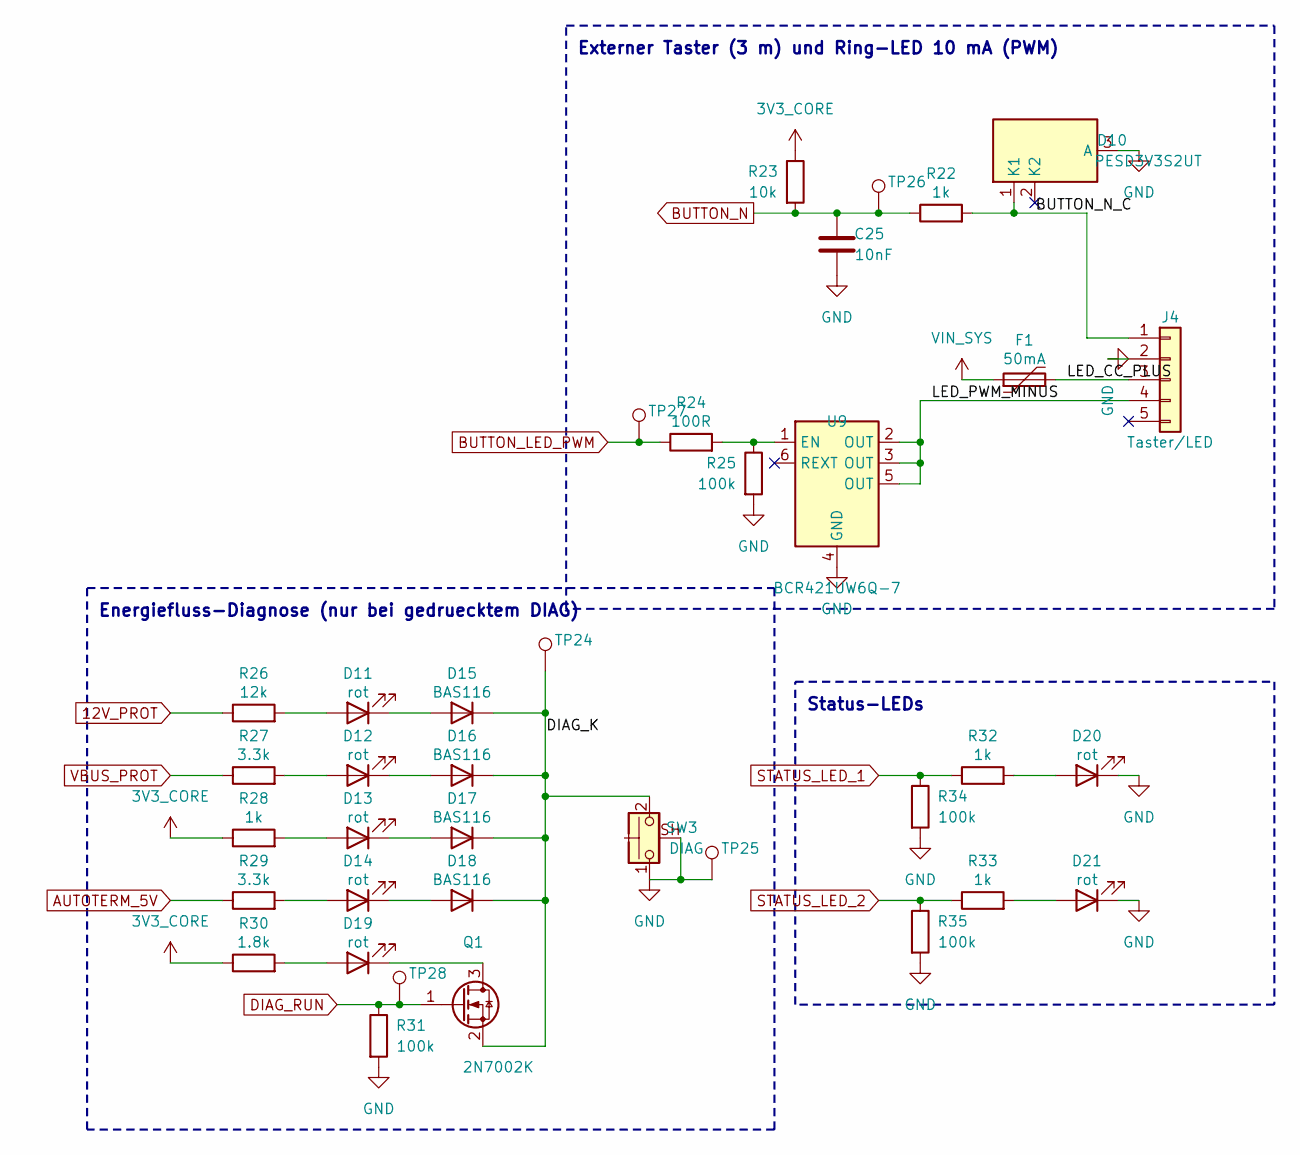
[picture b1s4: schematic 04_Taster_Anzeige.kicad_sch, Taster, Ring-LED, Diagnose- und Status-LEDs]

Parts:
C25: 10nF; C_0603_1608Metric
D10: PESD3V3S2UT; SOT-23; MPN PESD3V3S2UT,215; LCSC C84276
D11, D12, D13, D14, D19, D20, D21: rot; LED_0603_1608Metric; MPN LTST-C190KRKT; LCSC C94869
D15, D16, D17, D18: BAS116; SOT-23; MPN BAS116,215; LCSC C48502
F1: 50mA; Fuse_0805_2012Metric; MPN SMD0805-005/60N; LCSC C22366098
J4: Taster/LED; Molex_Nano-Fit_105313-xx05_1x05_P2.50mm_Horizontal; MPN 1053131305; LCSC C17316840
Q1: 2N7002K; SOT-23; MPN 2N7002K; LCSC C22379475
R22, R28, R32, R33: 1k; R_0603_1608Metric
R23: 10k; R_0603_1608Metric
R24: 100R; R_0603_1608Metric
R25, R31, R34, R35: 100k; R_0603_1608Metric
R26: 12k; R_0603_1608Metric
R27, R29: 3.3k; R_0603_1608Metric
R30: 1.8k; R_0603_1608Metric
SW3: DIAG; SW_Push_1P1T-SH_NO_CK_KMR2xxG; MPN KMR221GLFS; LCSC C72443
TP24: DIAG; TestPoint_Pad_D1.5mm
TP25: GND; TestPoint_Pad_D1.5mm
TP26: BUTTON_N; TestPoint_Pad_D1.5mm
TP27: BUTTON_LED_PWM; TestPoint_Pad_D1.5mm
TP28: DIAG_RUN; TestPoint_Pad_D1.5mm
U9: BCR421UW6Q-7; SOT-23-6; MPN BCR421UW6Q-7; LCSC C154739

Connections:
3V3_CORE: R23.1, R28.1, R30.1; also elsewhere on the board
12V_PROT: R26.1; also elsewhere on the board
/Taster und Anzeige/BUTTON_N_C: D10.1 (K1), J4.1, R22.2
/Taster und Anzeige/DIAG_K: D15.3 (K), D16.3 (K), D17.3 (K), D18.3 (K), Q1.2 (S), SW3.2, TP24.1 (1_1)
/Taster und Anzeige/LED_CC_PLUS: F1.2, J4.3
/Taster und Anzeige/LED_PWM_MINUS: J4.4, U9.2 (OUT), U9.3 (OUT), U9.5 (OUT)
AUTOTERM_5V: R29.1; also elsewhere on the board
BUTTON_LED_PWM: R24.1, TP27.1 (1_1); also elsewhere on the board
BUTTON_N: C25.1, R22.1, R23.2, TP26.1 (1_1); also elsewhere on the board
DIAG_RUN: Q1.1 (G), R31.1, TP28.1 (1_1); also elsewhere on the board
GND: C25.2, D10.3 (A), D20.1 (K), D21.1 (K), J4.2, R25.2, R31.2, R34.2, R35.2, SW3.1, SW3.SH (B), TP25.1 (1_1), U9.4 (GND); also elsewhere on the board
unnamed: D11.2 (A), R26.2
unnamed: D11.1 (K), D15.1 (A)
unnamed: D12.2 (A), R27.2
unnamed: D12.1 (K), D16.1 (A)
unnamed: D13.2 (A), R28.2
unnamed: D13.1 (K), D17.1 (A)
unnamed: D14.2 (A), R29.2
unnamed: D14.1 (K), D18.1 (A)
unnamed: D19.2 (A), R30.2
unnamed: D19.1 (K), Q1.3 (D)
unnamed: D20.2 (A), R32.2
unnamed: D21.2 (A), R33.2
unnamed: R24.2, R25.1, U9.1 (EN)
STATUS_LED_1: R32.1, R34.1; also elsewhere on the board
STATUS_LED_2: R33.1, R35.1; also elsewhere on the board
VBUS_PROT: R27.1; also elsewhere on the board
VIN_SYS: F1.1; also elsewhere on the board

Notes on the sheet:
Externer Taster (3 m) und Ring-LED 10 mA (PWM)
Status-LEDs
Energiefluss-Diagnose (nur bei gedruecktem DIAG)

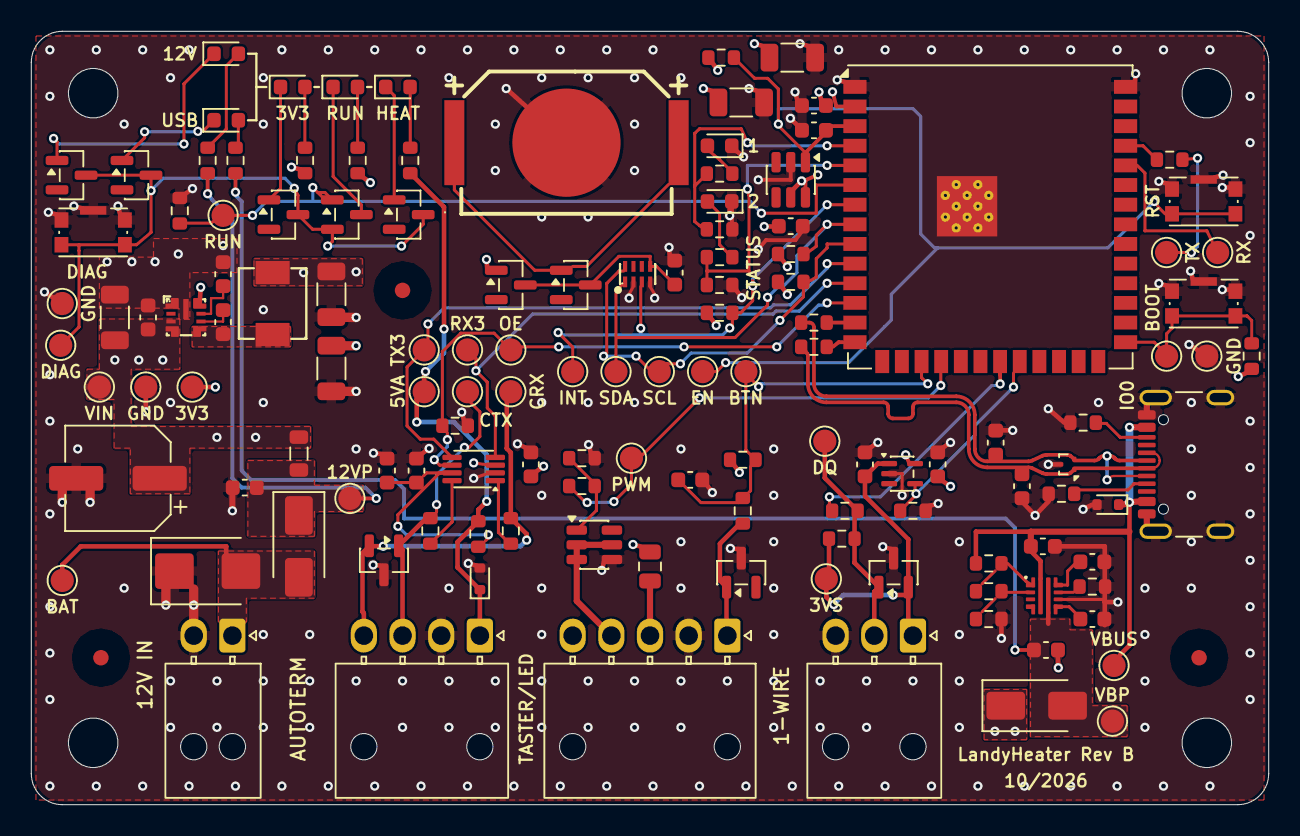
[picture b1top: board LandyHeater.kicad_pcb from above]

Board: 4 copper layers, 80.0 x 50.0 mm, 139 parts (0 on the bottom side), 66 nets.

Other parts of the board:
FID1, FID2, FID3: Fiducial; Fiducial_1mm_Mask2mm
H1, H2, H3, H4: M3; MountingHole_3.2mm_M3

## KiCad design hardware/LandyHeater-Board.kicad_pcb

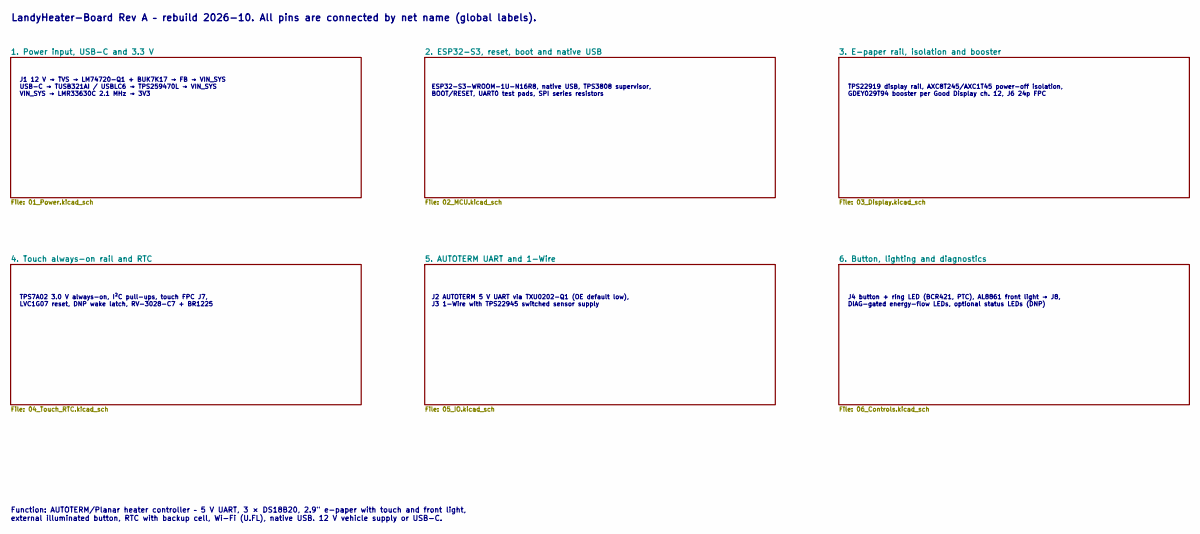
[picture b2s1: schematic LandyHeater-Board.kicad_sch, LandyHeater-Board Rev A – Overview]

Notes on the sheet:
J1 12 V → TVS → LM74720-Q1 + BUK7K17 → FB → VIN_SYS USB-C → TUSB321AI / USBLC6 → TPS259470L → VIN_SYS VIN_SYS → LMR33630C 2.1 MHz → 3V3
ESP32-S3-WROOM-1U-N16R8, native USB, TPS3808 supervisor, BOOT/RESET, UART0 test pads, SPI series resistors
TPS22919 display rail, AXC8T245/AXC1T45 power-off isolation, GDEY029T94 booster per Good Display ch. 12, J6 24p FPC
TPS7A02 3.0 V always-on, I²C pull-ups, touch FPC J7, LVC1G07 reset, DNP wake latch, RV-3028-C7 + BR1225
J2 AUTOTERM 5 V UART via TXU0202-Q1 (OE default low), J3 1-Wire with TPS22945 switched sensor supply
J4 button + ring LED (BCR421, PTC), AL8861 front light → J8, DIAG-gated energy-flow LEDs, optional status LEDs (DNP)
LandyHeater-Board Rev A – rebuild 2026-10. All pins are connected by net name (global labels).
Function: AUTOTERM/Planar heater controller – 5 V UART, 3 × DS18B20, 2.9" e-paper with touch and front light, external illuminated button, RTC with backup cell, Wi-Fi (U.FL), native USB. 12 V vehicle supply or USB-C.

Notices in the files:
parts and their libraries:
License: Apache-2.0
